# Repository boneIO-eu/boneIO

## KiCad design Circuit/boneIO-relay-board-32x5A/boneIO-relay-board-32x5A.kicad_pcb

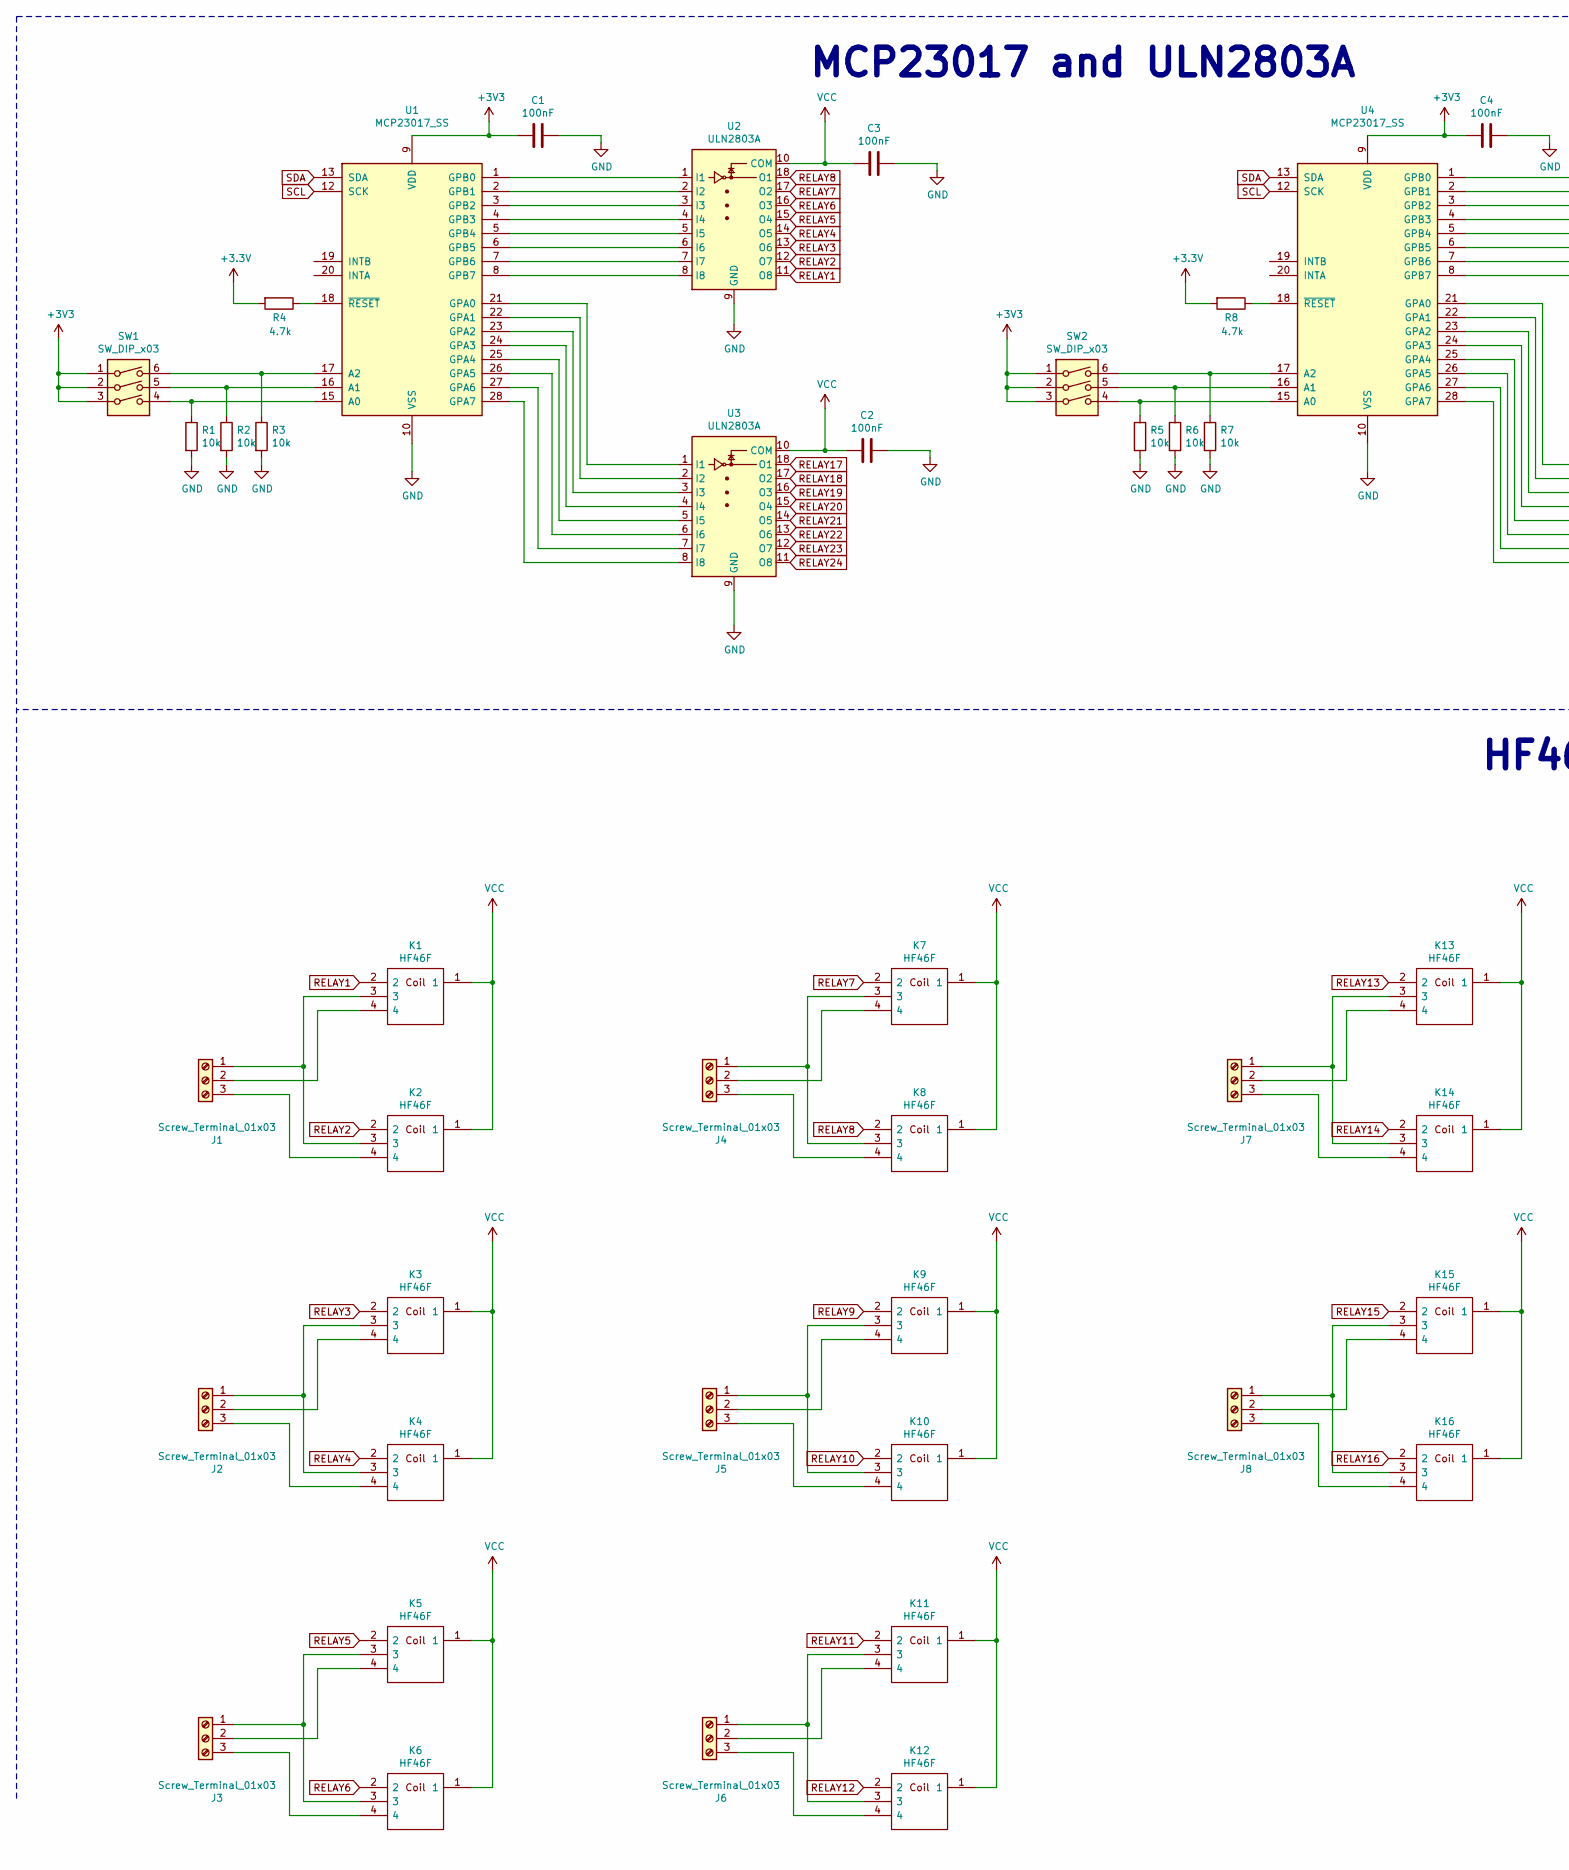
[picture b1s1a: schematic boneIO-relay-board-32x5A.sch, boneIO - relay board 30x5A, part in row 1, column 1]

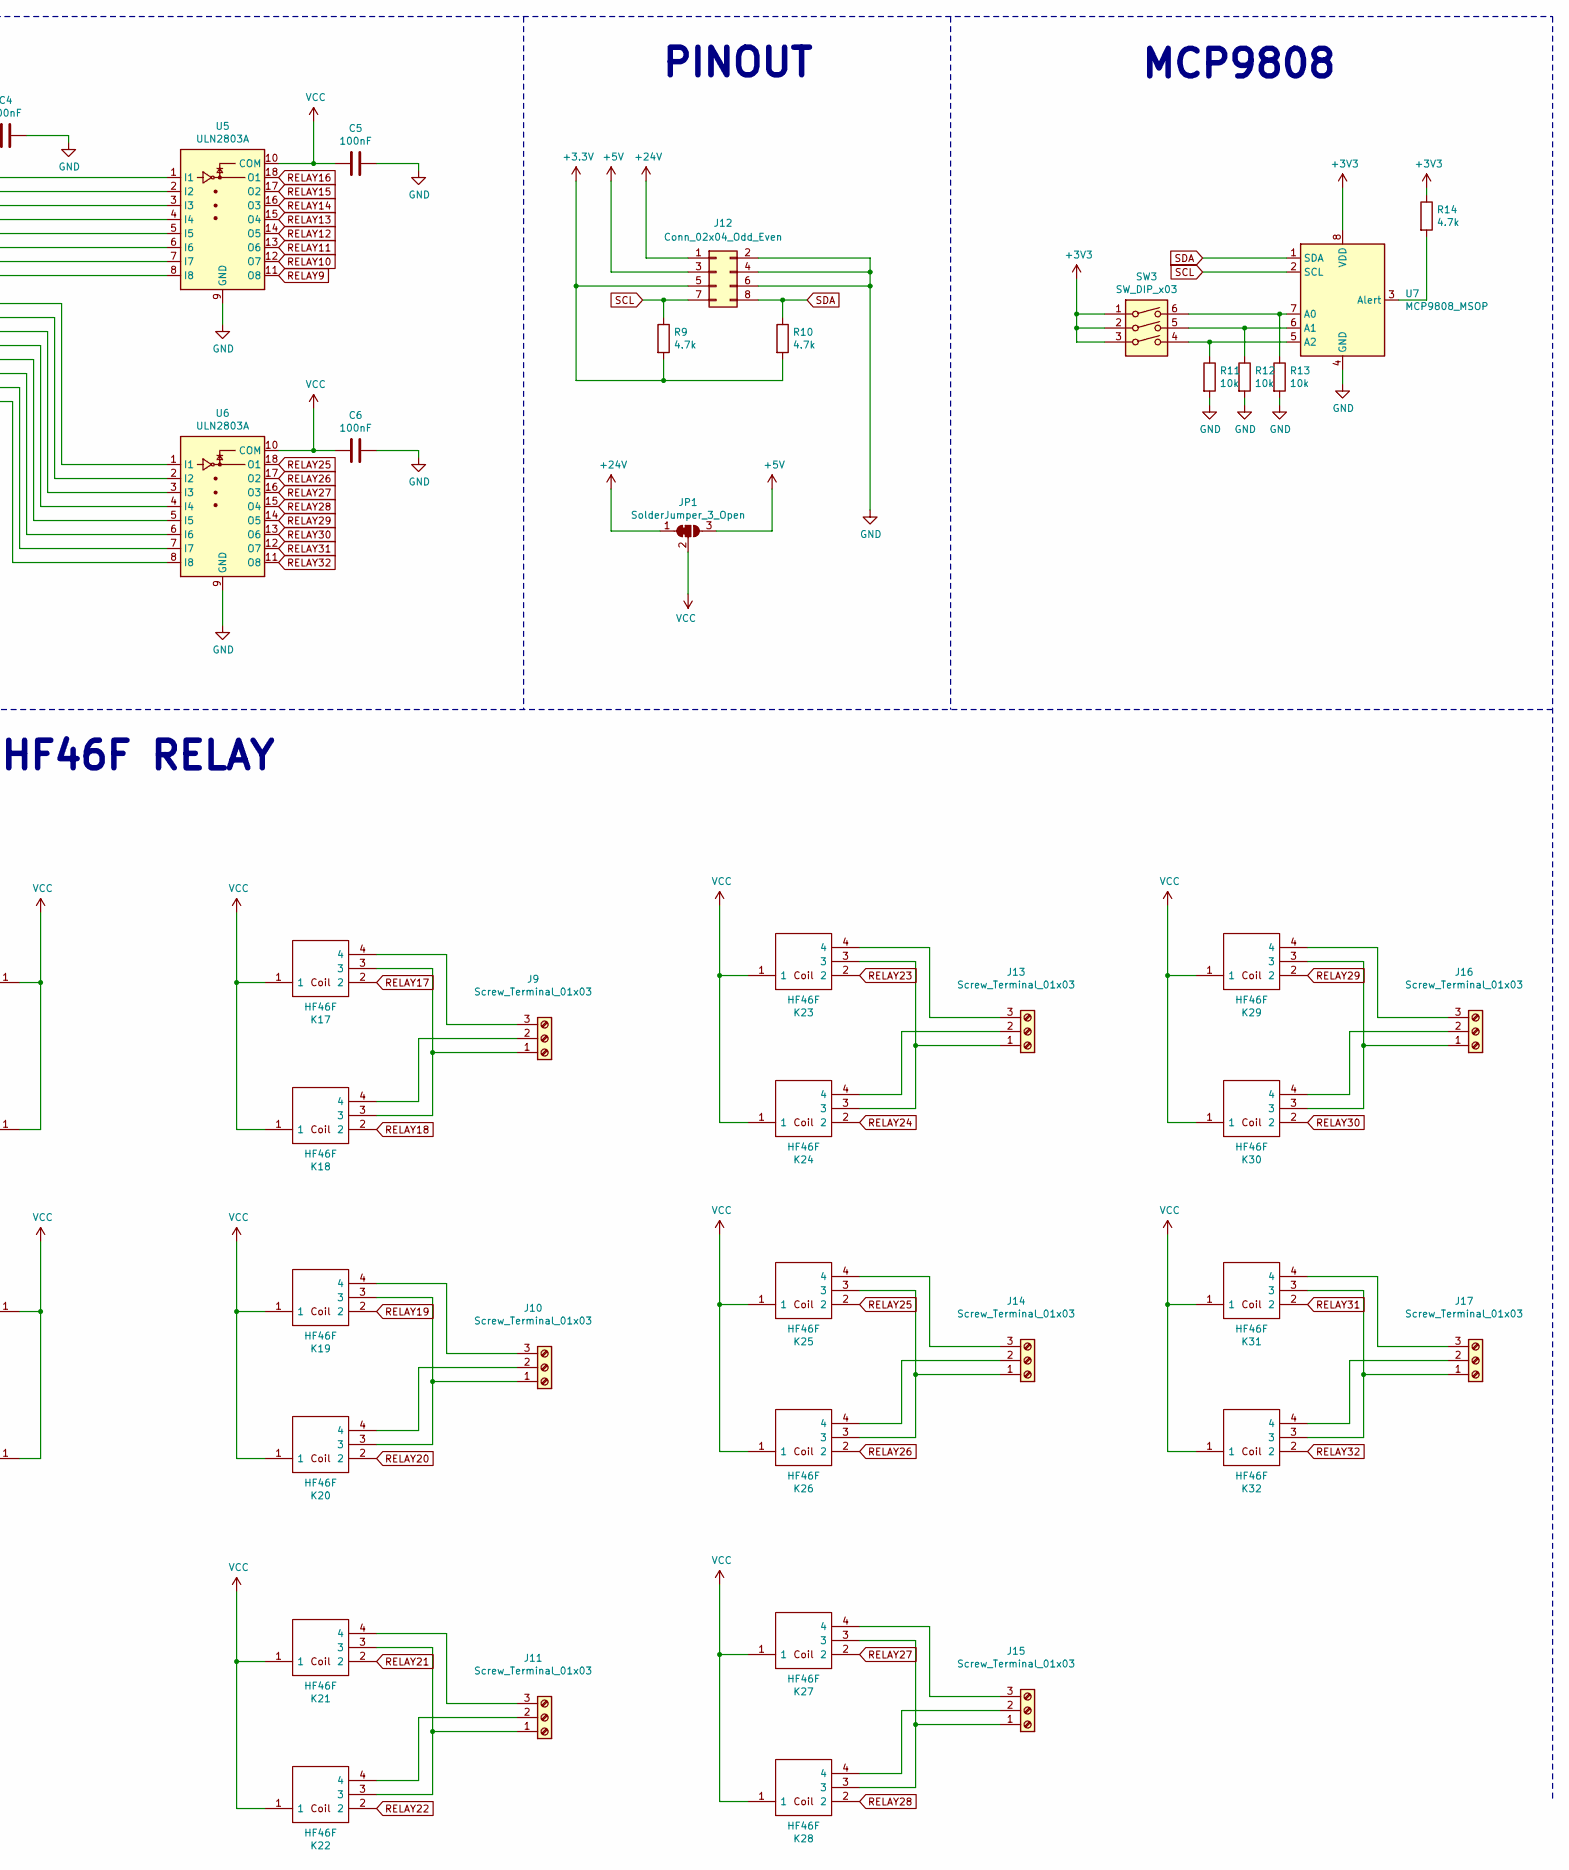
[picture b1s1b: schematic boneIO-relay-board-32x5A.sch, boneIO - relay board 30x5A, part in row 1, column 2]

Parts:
C1, C2, C3, C4, C5, C6: 100nF; C_0603_1608Metric
J1, J2, J3, J4, J5, J6, J7, J8, J9, J10, J11, J13, J14, J15, J16, J17: Screw_Terminal_01x03; PhoenixContact_GMSTBA_2,5_3-G_1x03_P7.50mm_Horizontal
J12: Conn_02x04_Odd_Even; PinHeader_2x04_P2.54mm_Vertical
JP1: SolderJumper_3_Open; SolderJumper-3_P1.3mm_Bridged12_RoundedPad1.0x1.5mm
K1, K2, K3, K4, K5, K6, K7, K8, K9, K10, K11, K12, K13, K14, K15, K16, K17, K18, K19, K20, K21, K22, K23, K24, K25, K26, K27, K28, K29, K30, K31, K32: HF46F; Manufacturer_Part_Number HF46F
R1, R2, R3, R5, R6, R7, R11, R12, R13: 10k; R_0603_1608Metric
R4, R8, R9, R10, R14: 4.7k; R_0603_1608Metric
SW1, SW2, SW3: SW_DIP_x03; SW_DIP_SPSTx03_Slide_KingTek_DSHP03TJ_W5.25mm_P1.27mm_JPin
U1, U4: MCP23017_SS; SSOP-28_5.3x10.2mm_P0.65mm
U2, U3, U5, U6: ULN2803A; SOIC-18W_7.5x11.6mm_P1.27mm
U7: MCP9808_MSOP; MSOP-8_3x3mm_P0.65mm

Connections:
+5V: J12.3, JP1.3 (B)
+24V: J12.1, JP1.1 (A)
GND: C1.1, C2.1, C3.1, C4.1, C5.1, C6.1, J12.2, J12.4, J12.6, R1.2, R2.2, R3.2, R5.2, R6.2, R7.2, R11.2, R12.2, R13.2, U1.10 (VSS), U2.9 (GND), U3.9 (GND), U4.10 (VSS), U5.9 (GND), U6.9 (GND), U7.4 (GND)
unnamed: J1.1, K1.3, K2.3
unnamed: J1.2, K1.4
unnamed: J1.3, K2.4
unnamed: J2.1, K3.3, K4.3
unnamed: J2.2, K3.4
unnamed: J2.3, K4.4
unnamed: J3.1, K5.3, K6.3
unnamed: J3.2, K5.4
unnamed: J3.3, K6.4
unnamed: J4.1, K7.3, K8.3
unnamed: J4.2, K7.4
unnamed: J4.3, K8.4
unnamed: J5.1, K9.3, K10.3
unnamed: J5.2, K9.4
unnamed: J5.3, K10.4
unnamed: J6.1, K11.3, K12.3
unnamed: J6.2, K11.4
unnamed: J6.3, K12.4
unnamed: J7.1, K13.3, K14.3
unnamed: J7.2, K13.4
unnamed: J7.3, K14.4
unnamed: J8.1, K15.3, K16.3
unnamed: J8.2, K15.4
unnamed: J8.3, K16.4
unnamed: J9.1, K17.3, K18.3
unnamed: J9.2, K18.4
unnamed: J9.3, K17.4
unnamed: J10.1, K19.3, K20.3
unnamed: J10.2, K20.4
unnamed: J10.3, K19.4
unnamed: J11.1, K21.3, K22.3
unnamed: J11.2, K22.4
unnamed: J11.3, K21.4
unnamed: J13.1, K23.3, K24.3
unnamed: J13.2, K24.4
unnamed: J13.3, K23.4
unnamed: J14.1, K25.3, K26.3
unnamed: J14.2, K26.4
unnamed: J14.3, K25.4
unnamed: J15.1, K27.3, K28.3
unnamed: J15.2, K28.4
unnamed: J15.3, K27.4
unnamed: J16.1, K29.3, K30.3
unnamed: J16.2, K30.4
unnamed: J16.3, K29.4
unnamed: J17.1, K31.3, K32.3
unnamed: J17.2, K32.4
unnamed: J17.3, K31.4
unnamed: R1.1, SW1.4, U1.15 (A0)
unnamed: R2.1, SW1.5, U1.16 (A1)
unnamed: R3.1, SW1.6, U1.17 (A2)
unnamed: R4.1, U1.18 (~RESET~)
unnamed: R5.1, SW2.4, U4.15 (A0)
unnamed: R6.1, SW2.5, U4.16 (A1)
unnamed: R7.1, SW2.6, U4.17 (A2)
unnamed: R8.1, U4.18 (~RESET~)
unnamed: R11.1, SW3.4, U7.5 (A2)
unnamed: R12.1, SW3.5, U7.6 (A1)
unnamed: R13.1, SW3.6, U7.7 (A0)
unnamed: R14.2, U7.3 (Alert)
unnamed: U1.1 (GPB0), U2.1 (I1)
unnamed: U1.2 (GPB1), U2.2 (I2)
unnamed: U1.3 (GPB2), U2.3 (I3)
unnamed: U1.4 (GPB3), U2.4 (I4)
unnamed: U1.5 (GPB4), U2.5 (I5)
unnamed: U1.6 (GPB5), U2.6 (I6)
unnamed: U1.7 (GPB6), U2.7 (I7)
unnamed: U1.8 (GPB7), U2.8 (I8)
unnamed: U1.21 (GPA0), U3.1 (I1)
unnamed: U1.22 (GPA1), U3.2 (I2)
unnamed: U1.23 (GPA2), U3.3 (I3)
unnamed: U1.24 (GPA3), U3.4 (I4)
unnamed: U1.25 (GPA4), U3.5 (I5)
unnamed: U1.26 (GPA5), U3.6 (I6)
unnamed: U1.27 (GPA6), U3.7 (I7)
unnamed: U1.28 (GPA7), U3.8 (I8)
unnamed: U4.1 (GPB0), U5.1 (I1)
unnamed: U4.2 (GPB1), U5.2 (I2)
unnamed: U4.3 (GPB2), U5.3 (I3)
unnamed: U4.4 (GPB3), U5.4 (I4)
unnamed: U4.5 (GPB4), U5.5 (I5)
unnamed: U4.6 (GPB5), U5.6 (I6)
unnamed: U4.7 (GPB6), U5.7 (I7)
unnamed: U4.8 (GPB7), U5.8 (I8)
unnamed: U4.21 (GPA0), U6.1 (I1)
unnamed: U4.22 (GPA1), U6.2 (I2)
unnamed: U4.23 (GPA2), U6.3 (I3)
unnamed: U4.24 (GPA3), U6.4 (I4)
unnamed: U4.25 (GPA4), U6.5 (I5)
unnamed: U4.26 (GPA5), U6.6 (I6)
unnamed: U4.27 (GPA6), U6.7 (I7)
unnamed: U4.28 (GPA7), U6.8 (I8)
RELAY1: K1.2, U2.11 (O8)
RELAY2: K2.2, U2.12 (O7)
RELAY3: K3.2, U2.13 (O6)
RELAY4: K4.2, U2.14 (O5)
RELAY5: K5.2, U2.15 (O4)
RELAY6: K6.2, U2.16 (O3)
RELAY7: K7.2, U2.17 (O2)
RELAY8: K8.2, U2.18 (O1)
RELAY9: K9.2, U5.11 (O8)
RELAY10: K10.2, U5.12 (O7)
RELAY11: K11.2, U5.13 (O6)
RELAY12: K12.2, U5.14 (O5)
RELAY13: K13.2, U5.15 (O4)
RELAY14: K14.2, U5.16 (O3)
RELAY15: K15.2, U5.17 (O2)
RELAY16: K16.2, U5.18 (O1)
RELAY17: K17.2, U3.18 (O1)
RELAY18: K18.2, U3.17 (O2)
RELAY19: K19.2, U3.16 (O3)
RELAY20: K20.2, U3.15 (O4)
RELAY21: K21.2, U3.14 (O5)
RELAY22: K22.2, U3.13 (O6)
RELAY23: K23.2, U3.12 (O7)
RELAY24: K24.2, U3.11 (O8)
RELAY25: K25.2, U6.18 (O1)
RELAY26: K26.2, U6.17 (O2)
RELAY27: K27.2, U6.16 (O3)
RELAY28: K28.2, U6.15 (O4)
RELAY29: K29.2, U6.14 (O5)
RELAY30: K30.2, U6.13 (O6)
RELAY31: K31.2, U6.12 (O7)
RELAY32: K32.2, U6.11 (O8)
SCL: J12.7, R9.1, U1.12 (SCK), U4.12 (SCK), U7.2 (SCL)
SDA: J12.8, R10.1, U1.13 (SDA), U4.13 (SDA), U7.1 (SDA)
VCC: C2.2, C3.2, C5.2, C6.2, JP1.2 (C), K1.1, K2.1, K3.1, K4.1, K5.1, K6.1, K7.1, K8.1, K9.1, K10.1, K11.1, K12.1, K13.1, K14.1, K15.1, K16.1, K17.1, K18.1, K19.1, K20.1, K21.1, K22.1, K23.1, K24.1, K25.1, K26.1, K27.1, K28.1, K29.1, K30.1, K31.1, K32.1, U2.10 (COM), U3.10 (COM), U5.10 (COM), U6.10 (COM)

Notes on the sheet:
PINOUT
MCP23017 and ULN2803A
HF46F RELAY
MCP9808

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
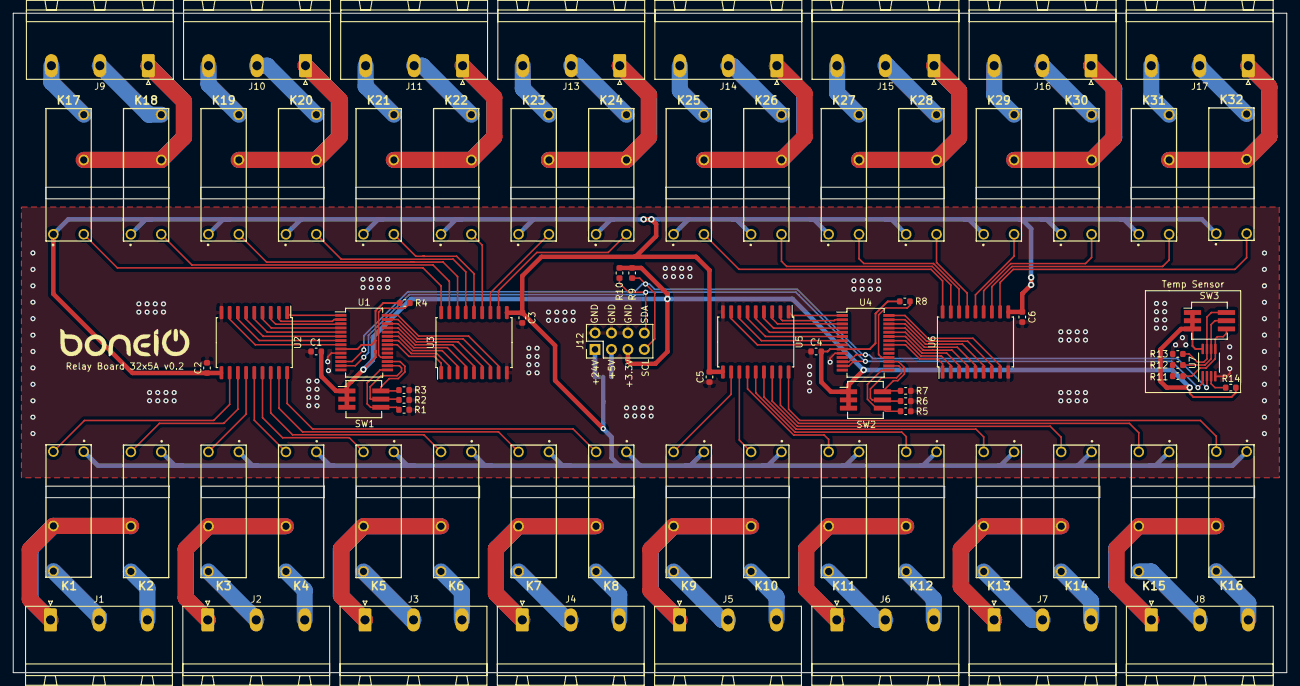
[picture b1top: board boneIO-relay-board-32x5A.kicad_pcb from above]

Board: 2 copper layers, 197.0 x 102.0 mm, 80 parts (1 on the bottom side), 131 nets.

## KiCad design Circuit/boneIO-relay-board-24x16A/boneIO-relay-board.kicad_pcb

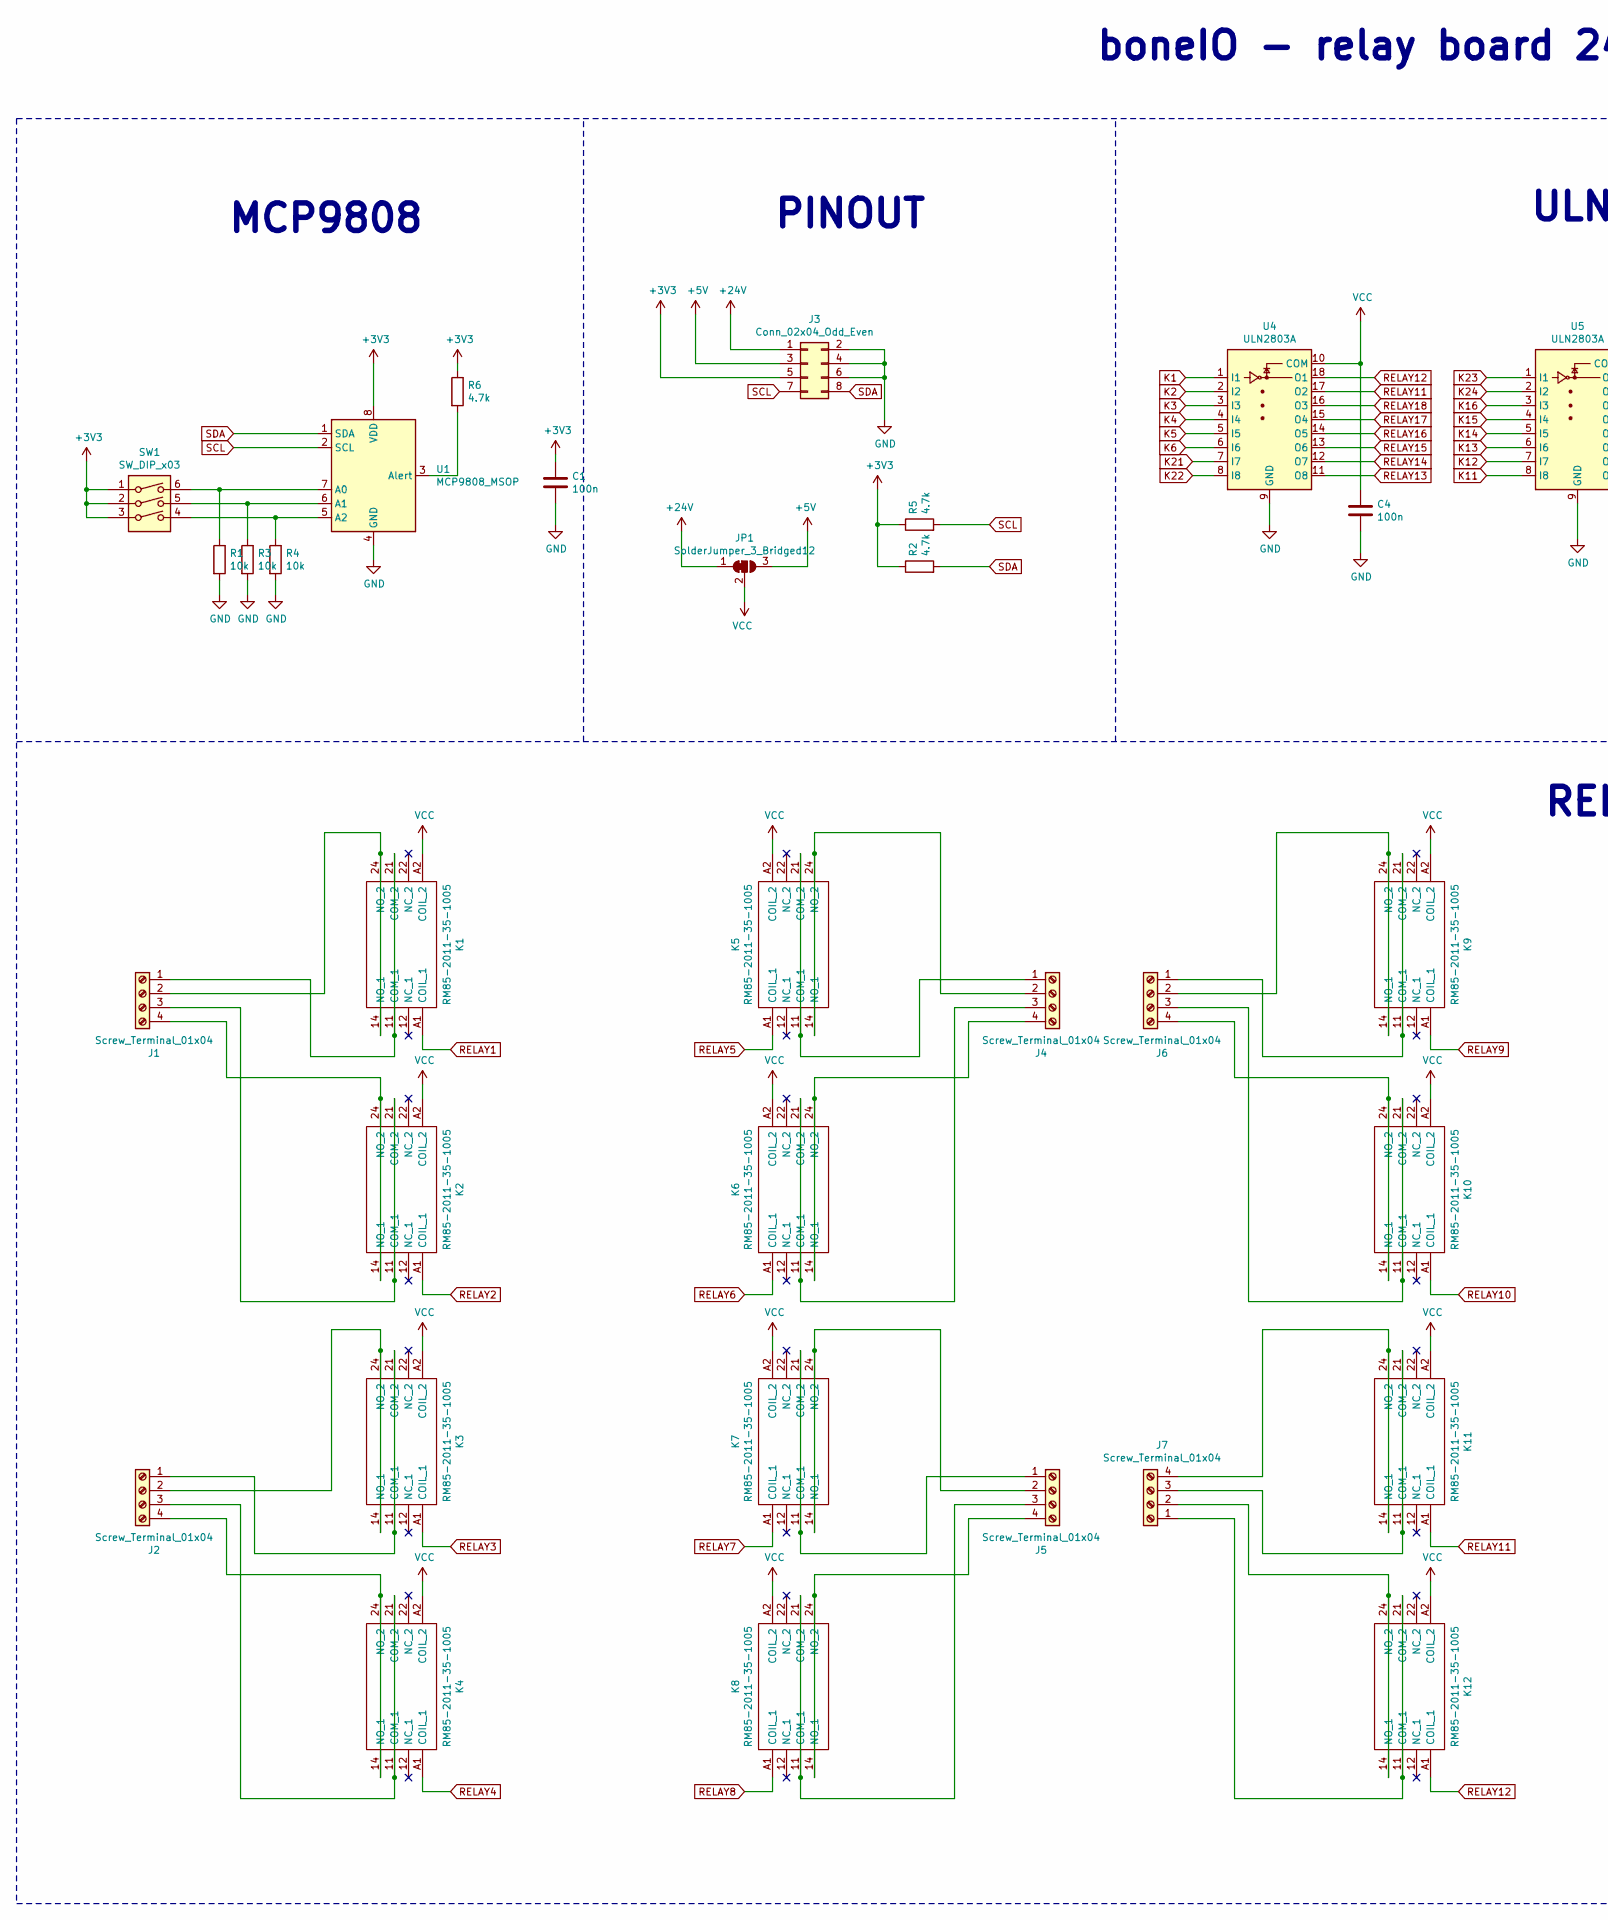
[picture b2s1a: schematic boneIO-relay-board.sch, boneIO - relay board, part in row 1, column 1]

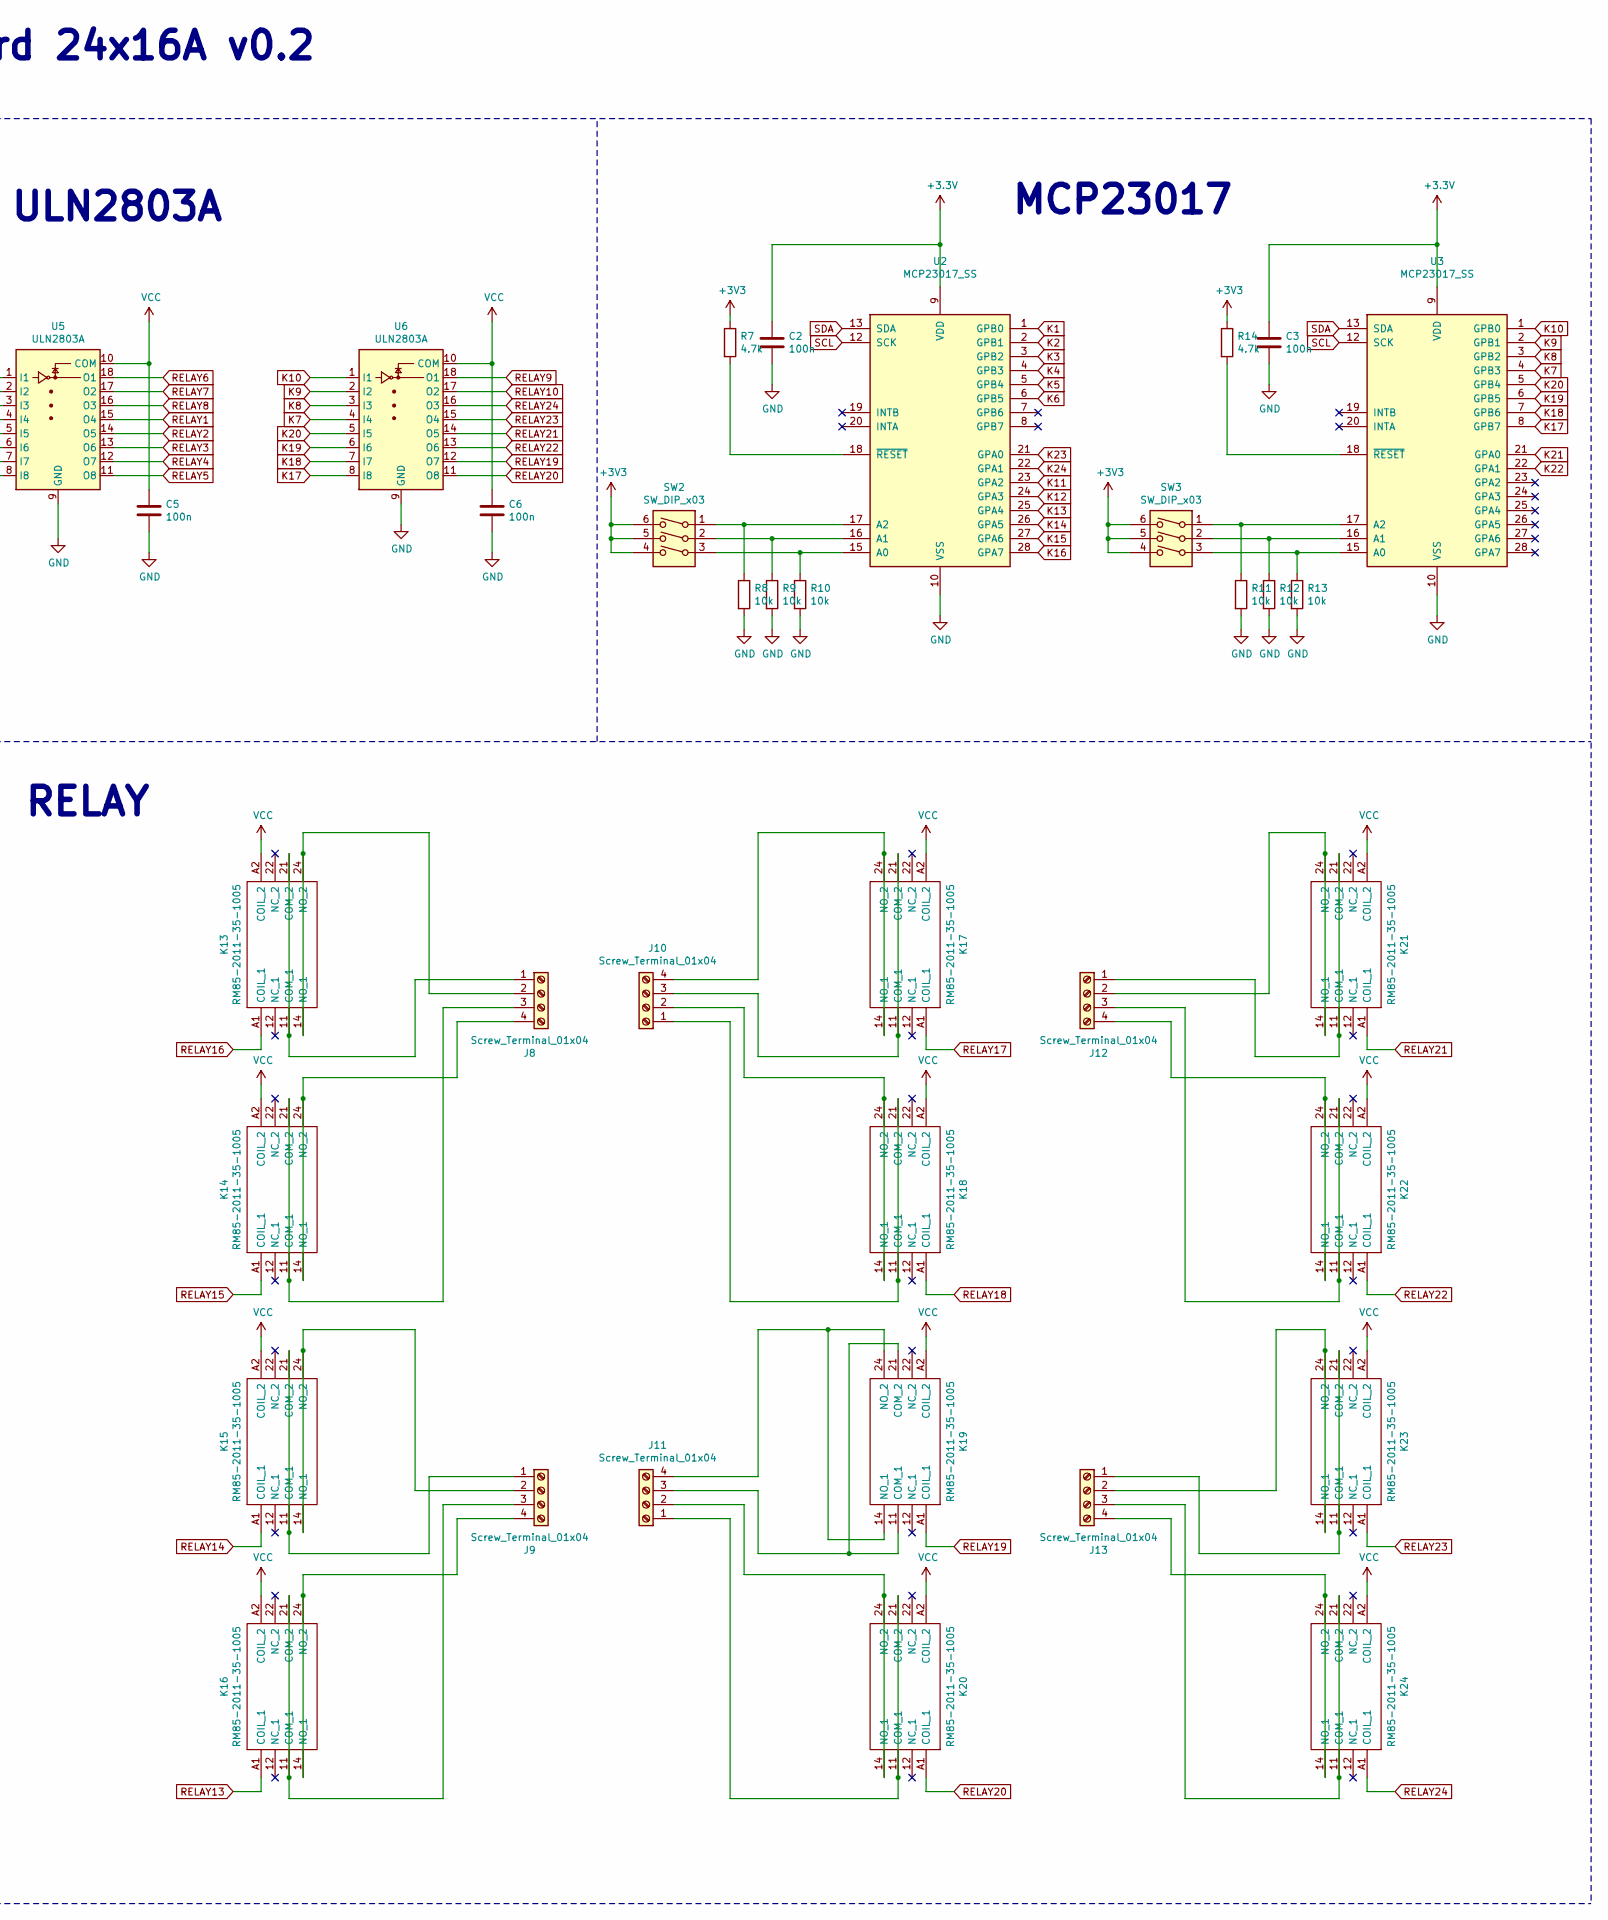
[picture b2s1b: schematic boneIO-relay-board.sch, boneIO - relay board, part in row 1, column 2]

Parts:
C1, C2, C3, C4, C5, C6: 100n; C_0603_1608Metric
J1, J2, J4, J5, J6, J7, J8, J9, J10, J11, J12, J13: Screw_Terminal_01x04; PhoenixContact_GMSTBA_2,5_4-G_1x04_P7.50mm_Horizontal
J3: Conn_02x04_Odd_Even; PinHeader_2x04_P2.54mm_Vertical
JP1: SolderJumper_3_Bridged12; SolderJumper-3_P1.3mm_Bridged12_RoundedPad1.0x1.5mm
K1, K2, K3, K4, K5, K6, K7, K8, K9, K10, K11, K12, K13, K14, K15, K16, K17, K18, K19, K20, K21, K22, K23, K24: RM85-2011-35-1005; RM852011351005_1; Manufacturer_Part_Number RM85-2011-35-1005
R1, R3, R4, R8, R9, R10, R11, R12, R13: 10k; R_0603_1608Metric
R2, R5, R6, R7, R14: 4.7k; R_0603_1608Metric
SW1, SW2, SW3: SW_DIP_x03; SW_DIP_SPSTx03_Slide_KingTek_DSHP03TJ_W5.25mm_P1.27mm_JPin
U1: MCP9808_MSOP; MSOP-8_3x3mm_P0.65mm
U2, U3: MCP23017_SS; SSOP-28_5.3x10.2mm_P0.65mm
U4, U5, U6: ULN2803A; SOIC-18W_7.5x11.6mm_P1.27mm

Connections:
+5V: J3.3, JP1.3 (B)
+24V: J3.1, JP1.1 (A)
GND: C1.2, C2.2, C3.2, C4.2, C5.2, C6.2, J3.2, J3.4, J3.6, R1.2, R3.2, R4.2, R8.2, R9.2, R10.2, R11.2, R12.2, R13.2, U1.4 (GND), U2.10 (VSS), U3.10 (VSS), U4.9 (GND), U5.9 (GND), U6.9 (GND)
K1: U2.1 (GPB0), U4.1 (I1)
K2: U2.2 (GPB1), U4.2 (I2)
K3: U2.3 (GPB2), U4.3 (I3)
K4: U2.4 (GPB3), U4.4 (I4)
K5: U2.5 (GPB4), U4.5 (I5)
K6: U2.6 (GPB5), U4.6 (I6)
K7: U3.4 (GPB3), U6.4 (I4)
K8: U3.3 (GPB2), U6.3 (I3)
K9: U3.2 (GPB1), U6.2 (I2)
K10: U3.1 (GPB0), U6.1 (I1)
K11: U2.23 (GPA2), U5.8 (I8)
K12: U2.24 (GPA3), U5.7 (I7)
K13: U2.25 (GPA4), U5.6 (I6)
K14: U2.26 (GPA5), U5.5 (I5)
K15: U2.27 (GPA6), U5.4 (I4)
K16: U2.28 (GPA7), U5.3 (I3)
K17: U3.8 (GPB7), U6.8 (I8)
K18: U3.7 (GPB6), U6.7 (I7)
K19: U3.6 (GPB5), U6.6 (I6)
K20: U3.5 (GPB4), U6.5 (I5)
K21: U3.21 (GPA0), U4.7 (I7)
K22: U3.22 (GPA1), U4.8 (I8)
K23: U2.21 (GPA0), U5.1 (I1)
K24: U2.22 (GPA1), U5.2 (I2)
unnamed: J1.1, K1.11 (COM_1), K1.21 (COM_2)
unnamed: J1.2, K1.14 (NO_1), K1.24 (NO_2)
unnamed: J1.3, K2.11 (COM_1), K2.21 (COM_2)
unnamed: J1.4, K2.14 (NO_1), K2.24 (NO_2)
unnamed: J2.1, K3.11 (COM_1), K3.21 (COM_2)
unnamed: J2.2, K3.14 (NO_1), K3.24 (NO_2)
unnamed: J2.3, K4.11 (COM_1), K4.21 (COM_2)
unnamed: J2.4, K4.14 (NO_1), K4.24 (NO_2)
unnamed: J4.1, K5.11 (COM_1), K5.21 (COM_2)
unnamed: J4.2, K5.14 (NO_1), K5.24 (NO_2)
unnamed: J4.3, K6.11 (COM_1), K6.21 (COM_2)
unnamed: J4.4, K6.14 (NO_1), K6.24 (NO_2)
unnamed: J5.1, K7.11 (COM_1), K7.21 (COM_2)
unnamed: J5.2, K7.14 (NO_1), K7.24 (NO_2)
unnamed: J5.3, K8.11 (COM_1), K8.21 (COM_2)
unnamed: J5.4, K8.14 (NO_1), K8.24 (NO_2)
unnamed: J6.1, K9.11 (COM_1), K9.21 (COM_2)
unnamed: J6.2, K9.14 (NO_1), K9.24 (NO_2)
unnamed: J6.3, K10.11 (COM_1), K10.21 (COM_2)
unnamed: J6.4, K10.14 (NO_1), K10.24 (NO_2)
unnamed: J7.1, K12.11 (COM_1), K12.21 (COM_2)
unnamed: J7.2, K12.14 (NO_1), K12.24 (NO_2)
unnamed: J7.3, K11.11 (COM_1), K11.21 (COM_2)
unnamed: J7.4, K11.14 (NO_1), K11.24 (NO_2)
unnamed: J8.1, K13.11 (COM_1), K13.21 (COM_2)
unnamed: J8.2, K13.14 (NO_1), K13.24 (NO_2)
unnamed: J8.3, K14.11 (COM_1), K14.21 (COM_2)
unnamed: J8.4, K14.14 (NO_1), K14.24 (NO_2)
unnamed: J9.1, K15.11 (COM_1), K15.21 (COM_2)
unnamed: J9.2, K15.14 (NO_1), K15.24 (NO_2)
unnamed: J9.3, K16.11 (COM_1), K16.21 (COM_2)
unnamed: J9.4, K16.14 (NO_1), K16.24 (NO_2)
unnamed: J10.1, K18.11 (COM_1), K18.21 (COM_2)
unnamed: J10.2, K18.14 (NO_1), K18.24 (NO_2)
unnamed: J10.3, K17.11 (COM_1), K17.21 (COM_2)
unnamed: J10.4, K17.14 (NO_1), K17.24 (NO_2)
unnamed: J11.1, K20.11 (COM_1), K20.21 (COM_2)
unnamed: J11.2, K20.14 (NO_1), K20.24 (NO_2)
unnamed: J11.3, K19.11 (COM_1), K19.21 (COM_2)
unnamed: J11.4, K19.14 (NO_1), K19.24 (NO_2)
unnamed: J12.1, K21.11 (COM_1), K21.21 (COM_2)
unnamed: J12.2, K21.14 (NO_1), K21.24 (NO_2)
unnamed: J12.3, K22.11 (COM_1), K22.21 (COM_2)
unnamed: J12.4, K22.14 (NO_1), K22.24 (NO_2)
unnamed: J13.1, K23.11 (COM_1), K23.21 (COM_2)
unnamed: J13.2, K23.14 (NO_1), K23.24 (NO_2)
unnamed: J13.3, K24.11 (COM_1), K24.21 (COM_2)
unnamed: J13.4, K24.14 (NO_1), K24.24 (NO_2)
unnamed: R1.1, SW1.6, U1.7 (A0)
unnamed: R3.1, SW1.5, U1.6 (A1)
unnamed: R4.1, SW1.4, U1.5 (A2)
unnamed: R6.2, U1.3 (Alert)
unnamed: R7.2, U2.18 (~RESET~)
unnamed: R8.1, SW2.1, U2.17 (A2)
unnamed: R9.1, SW2.2, U2.16 (A1)
unnamed: R10.1, SW2.3, U2.15 (A0)
unnamed: R11.1, SW3.1, U3.17 (A2)
unnamed: R12.1, SW3.2, U3.16 (A1)
unnamed: R13.1, SW3.3, U3.15 (A0)
unnamed: R14.2, U3.18 (~RESET~)
RELAY1: K1.A1 (COIL_1), U5.15 (O4)
RELAY2: K2.A1 (COIL_1), U5.14 (O5)
RELAY3: K3.A1 (COIL_1), U5.13 (O6)
RELAY4: K4.A1 (COIL_1), U5.12 (O7)
RELAY5: K5.A1 (COIL_1), U5.11 (O8)
RELAY6: K6.A1 (COIL_1), U5.18 (O1)
RELAY7: K7.A1 (COIL_1), U5.17 (O2)
RELAY8: K8.A1 (COIL_1), U5.16 (O3)
RELAY9: K9.A1 (COIL_1), U6.18 (O1)
RELAY10: K10.A1 (COIL_1), U6.17 (O2)
RELAY11: K11.A1 (COIL_1), U4.17 (O2)
RELAY12: K12.A1 (COIL_1), U4.18 (O1)
RELAY13: K16.A1 (COIL_1), U4.11 (O8)
RELAY14: K15.A1 (COIL_1), U4.12 (O7)
RELAY15: K14.A1 (COIL_1), U4.13 (O6)
RELAY16: K13.A1 (COIL_1), U4.14 (O5)
RELAY17: K17.A1 (COIL_1), U4.15 (O4)
RELAY18: K18.A1 (COIL_1), U4.16 (O3)
RELAY19: K19.A1 (COIL_1), U6.12 (O7)
RELAY20: K20.A1 (COIL_1), U6.11 (O8)
RELAY21: K21.A1 (COIL_1), U6.14 (O5)
RELAY22: K22.A1 (COIL_1), U6.13 (O6)
RELAY23: K23.A1 (COIL_1), U6.15 (O4)
RELAY24: K24.A1 (COIL_1), U6.16 (O3)
SCL: J3.7, R5.2, U1.2 (SCL), U2.12 (SCK), U3.12 (SCK)
SDA: J3.8, R2.2, U1.1 (SDA), U2.13 (SDA), U3.13 (SDA)
VCC: C4.1, C5.1, C6.1, JP1.2 (C), K1.A2 (COIL_2), K2.A2 (COIL_2), K3.A2 (COIL_2), K4.A2 (COIL_2), K5.A2 (COIL_2), K6.A2 (COIL_2), K7.A2 (COIL_2), K8.A2 (COIL_2), K9.A2 (COIL_2), K10.A2 (COIL_2), K11.A2 (COIL_2), K12.A2 (COIL_2), K13.A2 (COIL_2), K14.A2 (COIL_2), K15.A2 (COIL_2), K16.A2 (COIL_2), K17.A2 (COIL_2), K18.A2 (COIL_2), K19.A2 (COIL_2), K20.A2 (COIL_2), K21.A2 (COIL_2), K22.A2 (COIL_2), K23.A2 (COIL_2), K24.A2 (COIL_2), U4.10 (COM), U5.10 (COM), U6.10 (COM)

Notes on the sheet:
PINOUT
ULN2803A
RELAY
MCP9808
MCP23017
boneIO - relay board 24x16A v0.2

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
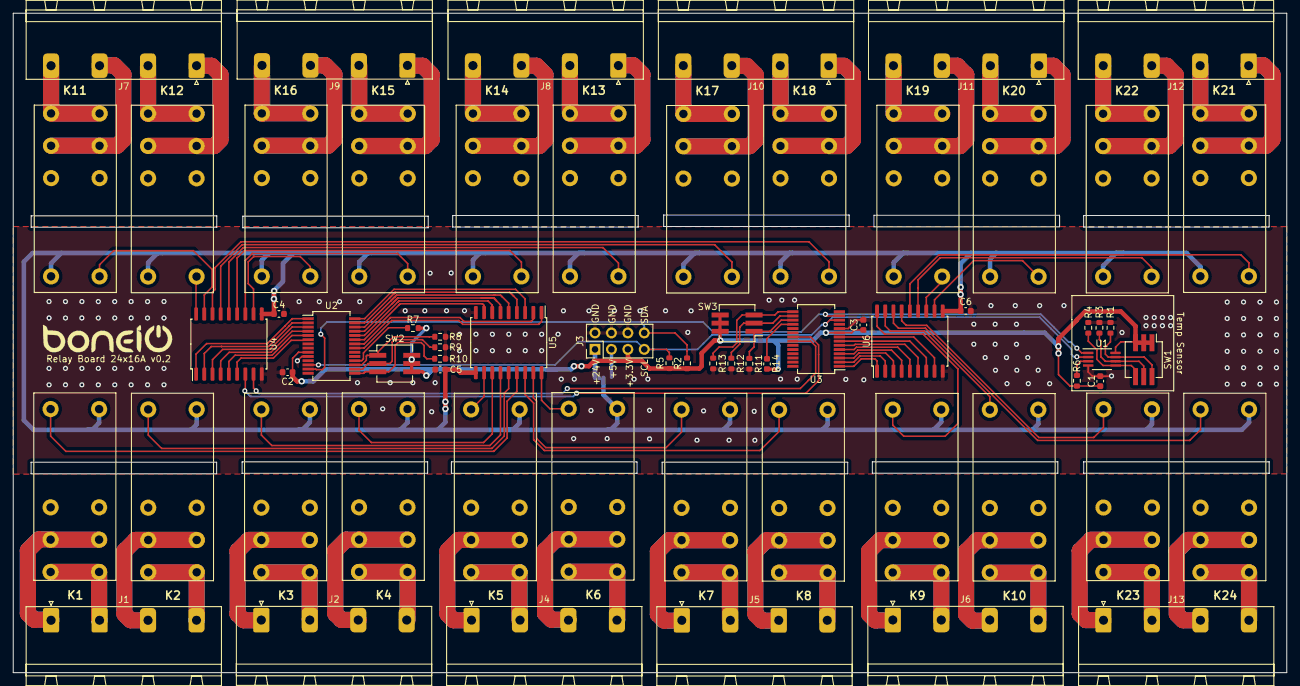
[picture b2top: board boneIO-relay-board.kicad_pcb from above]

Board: 2 copper layers, 197.0 x 102.0 mm, 67 parts (1 on the bottom side), 115 nets.
